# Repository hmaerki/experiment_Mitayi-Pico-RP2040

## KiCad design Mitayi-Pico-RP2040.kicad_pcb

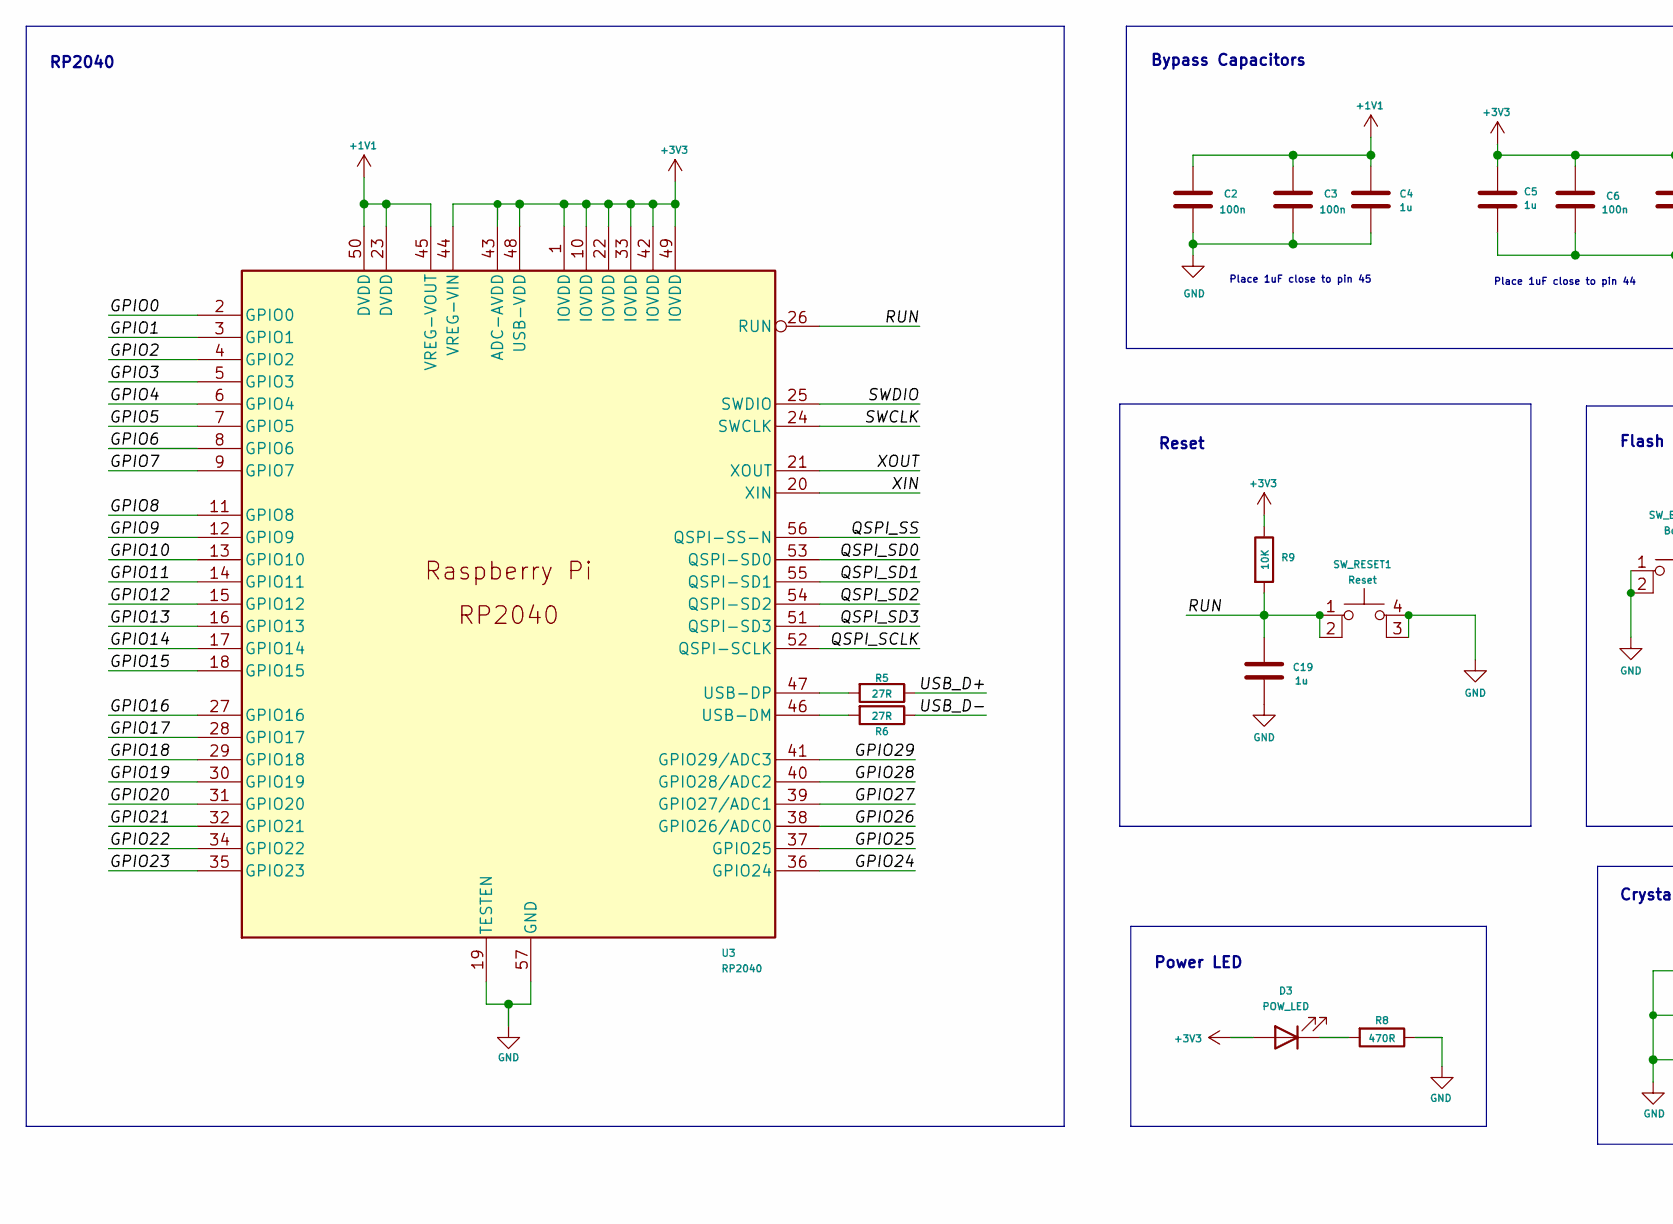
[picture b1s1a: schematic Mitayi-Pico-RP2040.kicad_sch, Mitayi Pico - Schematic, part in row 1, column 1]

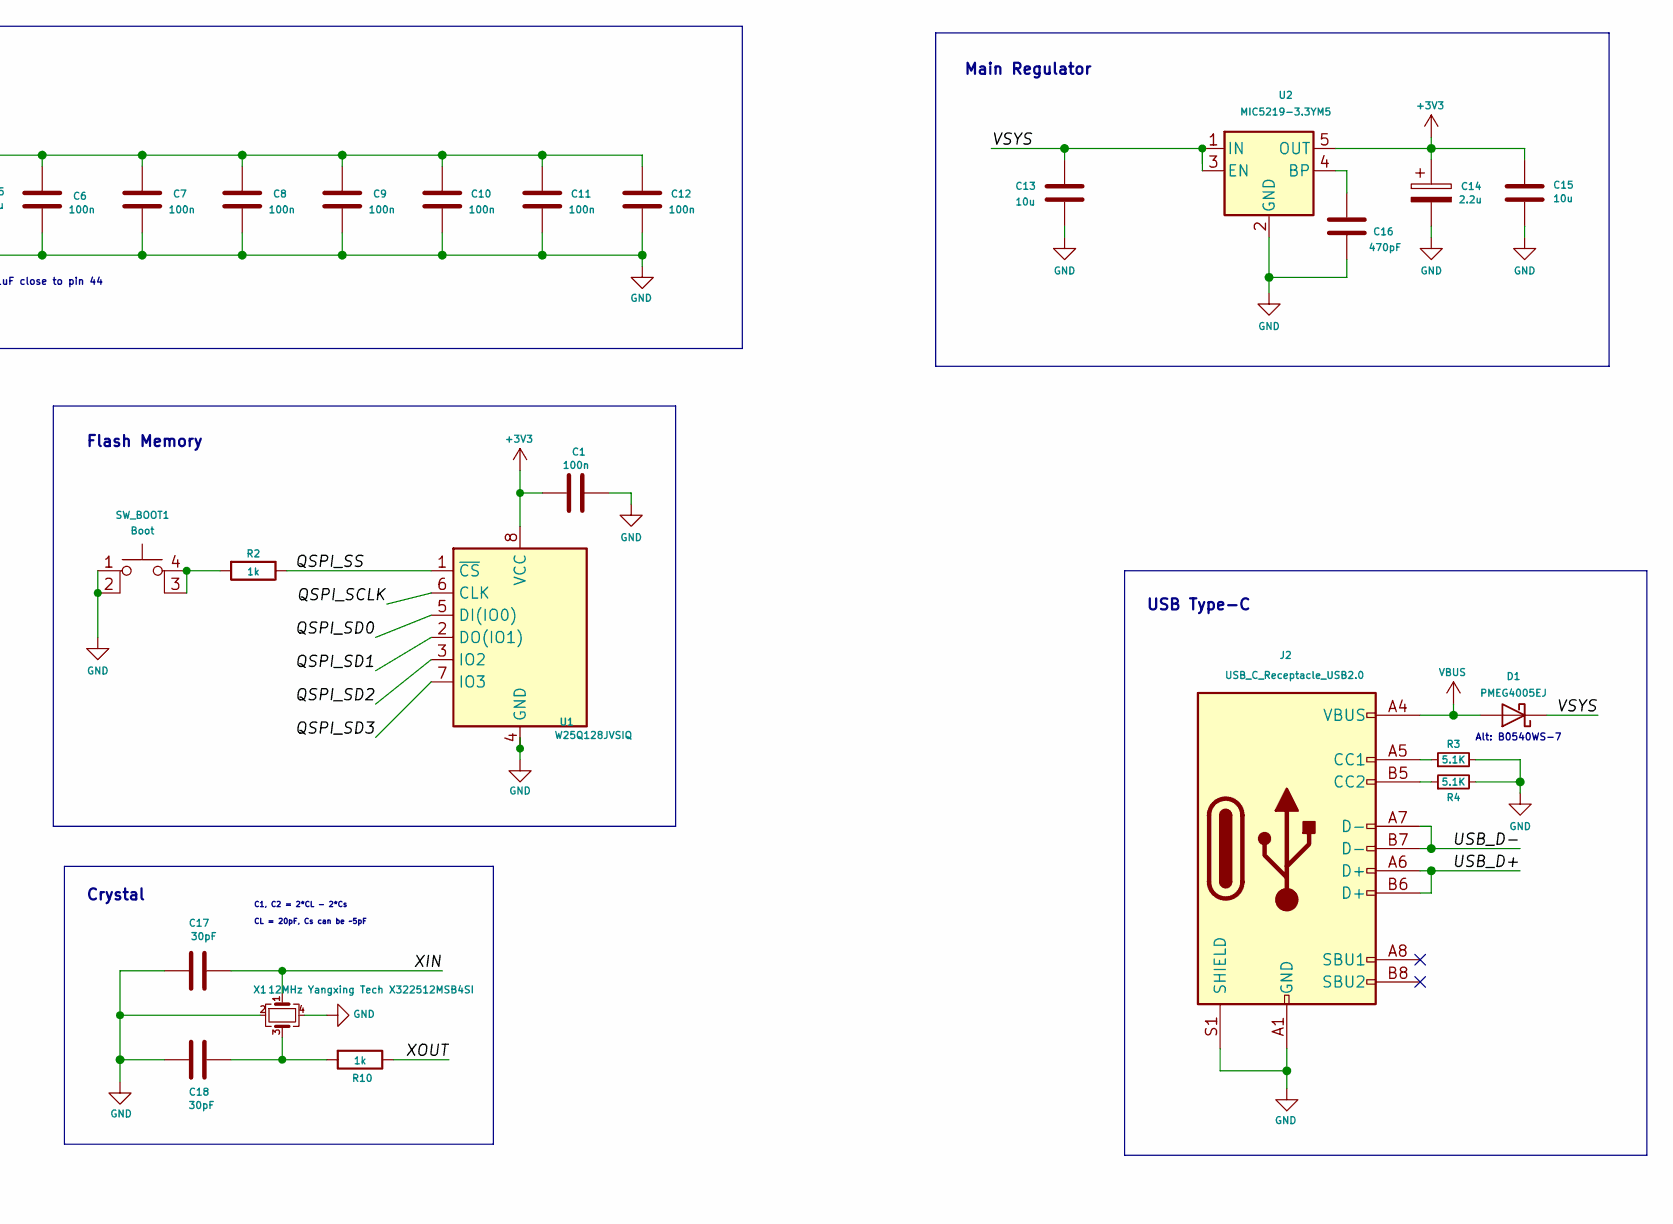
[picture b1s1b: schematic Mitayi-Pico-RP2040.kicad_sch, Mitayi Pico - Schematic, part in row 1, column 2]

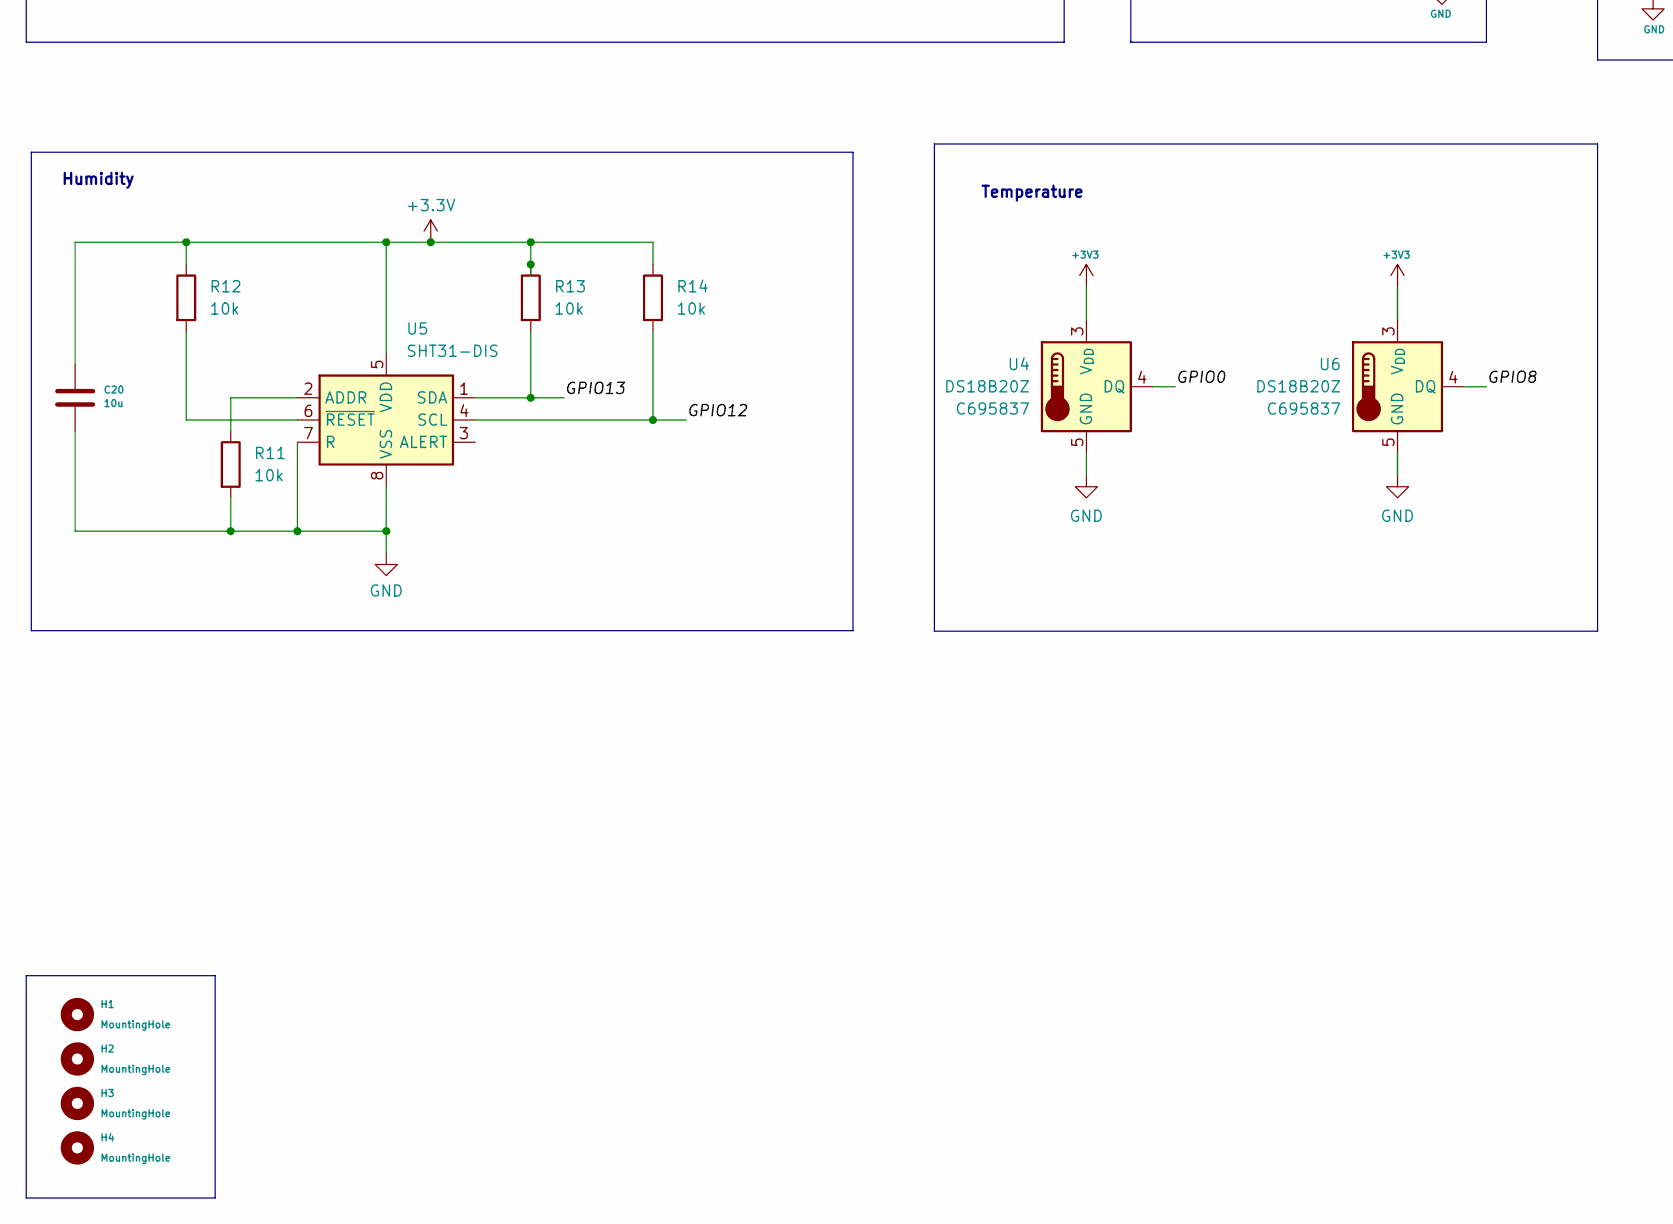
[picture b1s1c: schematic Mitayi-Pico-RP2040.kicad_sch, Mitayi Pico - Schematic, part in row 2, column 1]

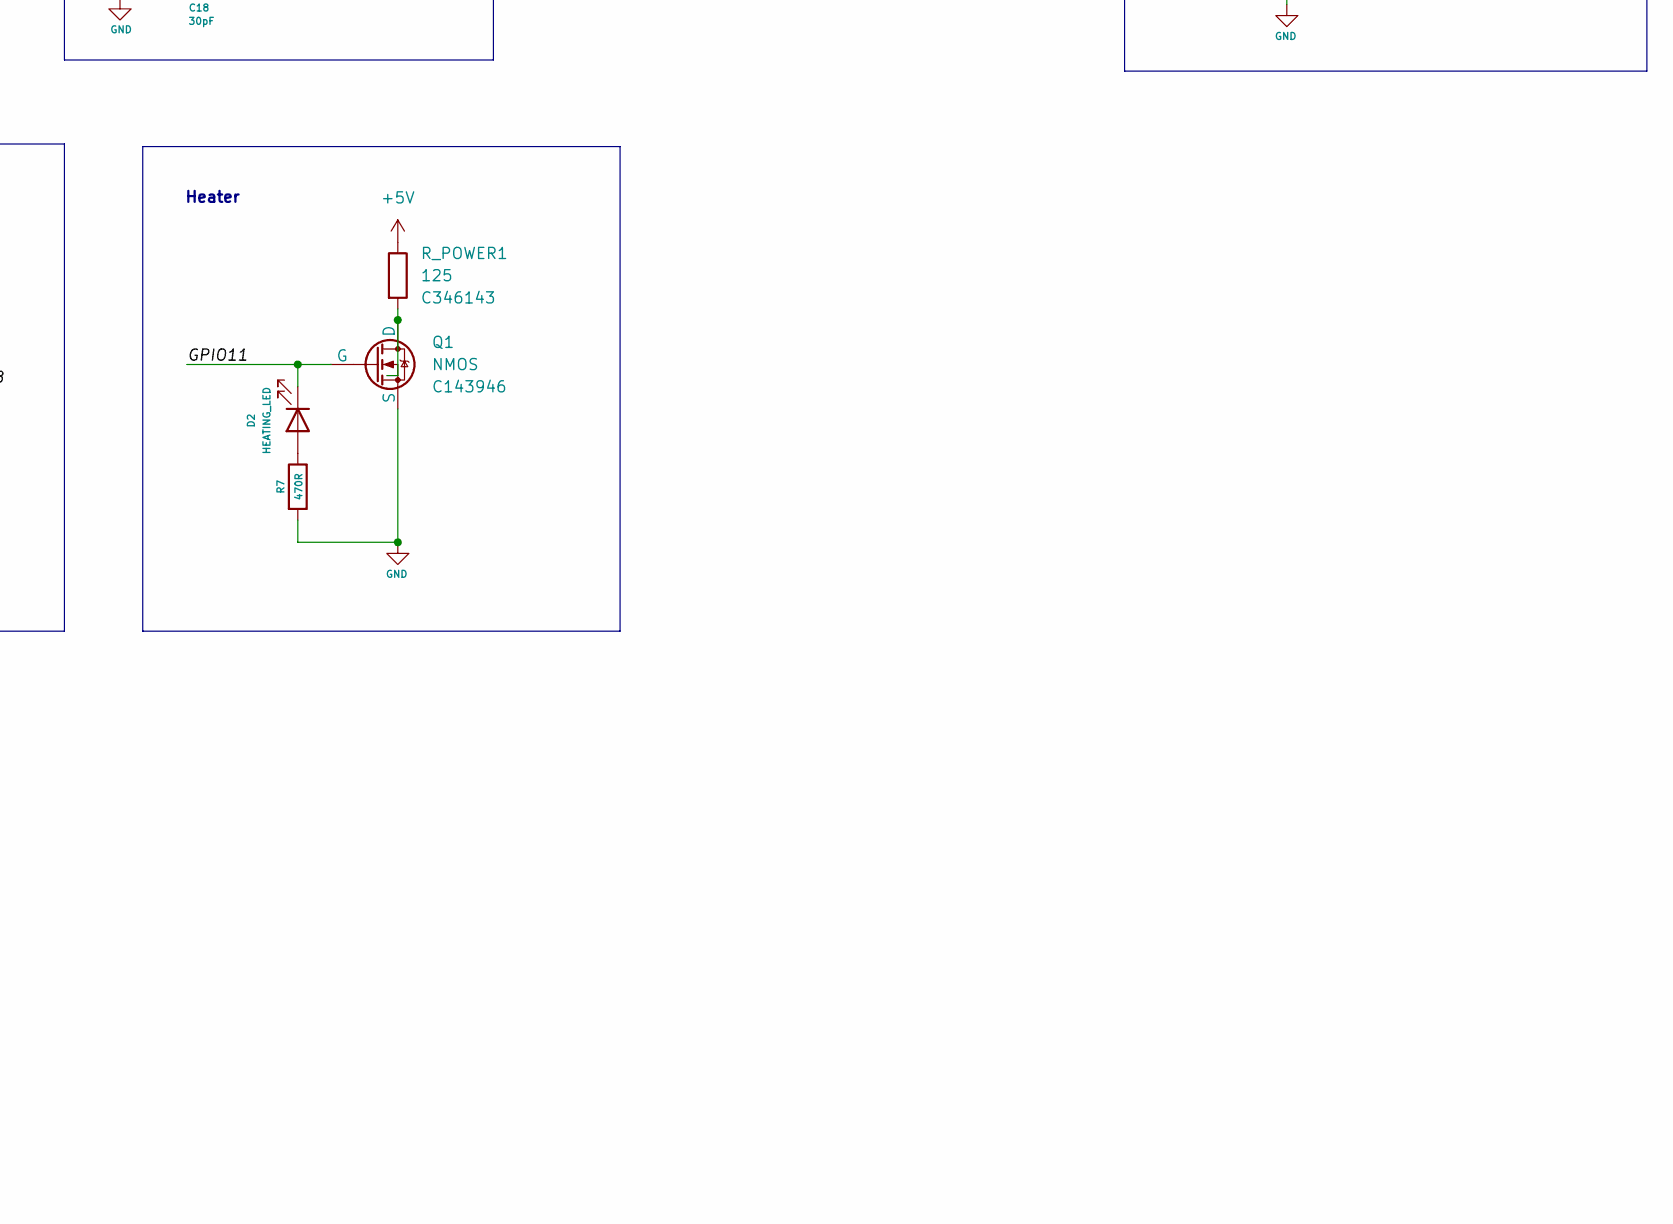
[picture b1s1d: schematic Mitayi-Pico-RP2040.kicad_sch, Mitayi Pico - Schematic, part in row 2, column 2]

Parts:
C1, C2, C3, C6, C7, C8, C9, C10, C11, C12: 100n; C_0402_1005Metric_Pad0.74x0.62mm_HandSolder
C4, C5, C19: 1u; C_0402_1005Metric_Pad0.74x0.62mm_HandSolder
C13, C15, C20: 10u; C_0603_1608Metric
C14: 2.2u; C_0402_1005Metric; JLC C12530
C16: 470pF; C_0402_1005Metric_Pad0.74x0.62mm_HandSolder
C17, C18: 30pF; C_0402_1005Metric_Pad0.74x0.62mm_HandSolder
D1: PMEG4005EJ; D_SOD-123F
D2: HEATING_LED; LED_0603_1608Metric
D3: POW_LED; LED_0603_1608Metric
H1, H2, H3, H4: MountingHole; MountingHole_2.2mm_M2
J2: USB_C_Receptacle_USB2.0; Korean-Hroparts-Elec_TYPE-C-31-M-12; JLC C5337088
Q1: NMOS; SOT-23; JLC Part C143946
R2, R10: 1k; R_0402_1005Metric_Pad0.72x0.64mm_HandSolder
R3, R4: 5.1K; R_0402_1005Metric_Pad0.72x0.64mm_HandSolder
R5, R6: 27R; R_0402_1005Metric_Pad0.72x0.64mm_HandSolder
R7, R8: 470R; R_0402_1005Metric_Pad0.72x0.64mm_HandSolder
R9: 10K; R_0402_1005Metric_Pad0.72x0.64mm_HandSolder
R11, R12, R13, R14: 10k; R_0402_1005Metric_Pad0.72x0.64mm_HandSolder
R_POWER1: 125; R_1210_3225Metric; JLC Part C346143
SW_BOOT1: Boot; SW_TS-1187A-B-A-B; JLC C318884
SW_RESET1: Reset; SW_TS-1187A-B-A-B; JLC C318884
U1: W25Q128JVSIQ; SOIC-8_5.23x5.23mm_P1.27mm
U2: MIC5219-3.3YM5; SOT-23-5
U3: RP2040; RP2040-QFN-56
U4, U6: DS18B20Z; SOIC-8_3.9x4.9mm_P1.27mm; JLC Part C695837
U5: SHT31-DIS; SON50P250X250X90-9T110X180N; JLC C80862
X1: 12MHz Yangxing Tech X322512MSB4SI; Crystal_SMD_3225-4Pin_3.2x2.5mm; JLC C9002

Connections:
+1V1: C2.1, C3.1, C4.1, U3.23 (DVDD), U3.45 (VREG-VOUT), U3.50 (DVDD)
+3.3V: C20.1, R12.1, R13.1, R14.1, U5.5 (VDD)
+3V3: C1.1, C5.1, C6.1, C7.1, C8.1, C9.1, C10.1, C11.1, C12.1, C14.1, C15.1, D3.2 (A), R9.1, U1.8 (VCC), U2.5 (OUT), U3.1 (IOVDD), U3.10 (IOVDD), U3.22 (IOVDD), U3.33 (IOVDD), U3.42 (IOVDD), U3.43 (ADC-AVDD), U3.44 (VREG-VIN), U3.48 (USB-VDD), U3.49 (IOVDD), U4.3 (V_{DD}), U6.3 (V_{DD})
+5V: R_POWER1.1
/GPIO0: U3.2 (GPIO0), U4.4 (DQ)
/GPIO1: U3.3 (GPIO1)
/GPIO2: U3.4 (GPIO2)
/GPIO3: U3.5 (GPIO3)
/GPIO4: U3.6 (GPIO4)
/GPIO5: U3.7 (GPIO5)
/GPIO6: U3.8 (GPIO6)
/GPIO7: U3.9 (GPIO7)
/GPIO8: U3.11 (GPIO8), U6.4 (DQ)
/GPIO9: U3.12 (GPIO9)
/GPIO10: U3.13 (GPIO10)
/GPIO11: D2.1 (K), Q1.2 (G), U3.14 (GPIO11)
/GPIO12: R14.2, U3.15 (GPIO12), U5.4 (SCL)
/GPIO13: R13.2, U3.16 (GPIO13), U5.1 (SDA)
/GPIO14: U3.17 (GPIO14)
/GPIO15: U3.18 (GPIO15)
/GPIO16: U3.27 (GPIO16)
/GPIO17: U3.28 (GPIO17)
/GPIO18: U3.29 (GPIO18)
/GPIO19: U3.30 (GPIO19)
/GPIO20: U3.31 (GPIO20)
/GPIO21: U3.32 (GPIO21)
/GPIO22: U3.34 (GPIO22)
/GPIO23: U3.35 (GPIO23)
/GPIO24: U3.36 (GPIO24)
/GPIO25: U3.37 (GPIO25)
/GPIO26: U3.38 (GPIO26/ADC0)
/GPIO27: U3.39 (GPIO27/ADC1)
/GPIO28: U3.40 (GPIO28/ADC2)
/GPIO29: U3.41 (GPIO29/ADC3)
/QSPI_SCLK: U1.6 (CLK), U3.52 (QSPI-SCLK)
/QSPI_SD0: U1.5 (DI(IO0)), U3.53 (QSPI-SD0)
/QSPI_SD1: U1.2 (DO(IO1)), U3.55 (QSPI-SD1)
/QSPI_SD2: U1.3 (IO2), U3.54 (QSPI-SD2)
/QSPI_SD3: U1.7 (IO3), U3.51 (QSPI-SD3)
/QSPI_SS: R2.1, U1.1 (~CS), U3.56 (QSPI-SS-N)
/RUN: C19.1, R9.2, SW_RESET1.1, SW_RESET1.2, U3.26 (RUN)
/SWCLK: U3.24 (SWCLK)
/SWDIO: U3.25 (SWDIO)
/USB_D+: J2.A6 (D+), J2.B6 (D+), R5.1
/USB_D-: J2.A7 (D-), J2.B7 (D-), R6.1
/VSYS: C13.1, D1.1 (K), U2.1 (IN), U2.3 (EN)
/XIN: C17.1, U3.20 (XIN), X1.1
/XOUT: R10.1, U3.21 (XOUT)
GND: C1.2, C2.2, C4.2, C5.2, C6.2, C7.2, C8.2, C9.2, C10.2, C11.2, C12.2, C13.2, C14.2, C15.2, C16.2, C17.2, C18.2, C19.2, C20.2, J2.A1 (GND), J2.A12 (GND), J2.B1 (GND), J2.B12 (GND), J2.S1 (SHIELD), Q1.3 (S), R3.2, R4.2, R7.2, R8.1, R11.2, SW_BOOT1.1, SW_BOOT1.2, SW_RESET1.3 (K), SW_RESET1.4 (A), U1.4 (GND), U2.2 (GND), U3.19 (TESTEN), U3.57 (GND), U4.5 (GND), U5.7 (R), U5.8 (VSS), U5.9 (VSS), U6.5 (GND), X1.2, X1.4
unnamed: C18.1, R10.2, X1.3
unnamed: D2.2 (A), R7.1
unnamed: D3.1 (K), R8.2
unnamed: J2.A5 (CC1), R3.1
unnamed: J2.B5 (CC2), R4.1
unnamed: Q1.1 (D), R_POWER1.2
unnamed: R2.2, SW_BOOT1.3 (K), SW_BOOT1.4 (A)
unnamed: C16.1, U2.4 (BP)
unnamed: R6.2, U3.46 (USB-DM)
unnamed: R5.2, U3.47 (USB-DP)
unnamed: R11.1, U5.2 (ADDR)
unnamed: R12.2, U5.6 (~RESET)
VBUS: D1.2 (A), J2.A4 (VBUS), J2.A9 (VBUS), J2.B4 (VBUS), J2.B9 (VBUS)

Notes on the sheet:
USB Type-C
Main Regulator
RP2040
Alt: B0540WS-7
Bypass Capacitors
Place 1uF close to pin 45
Heater
Crystal
Power LED
C1, C2 = 2*CL - 2*Cs CL = 20pF, Cs can be ~5pF
Reset
Place 1uF close to pin 44
Humidity
Flash Memory
Temperature

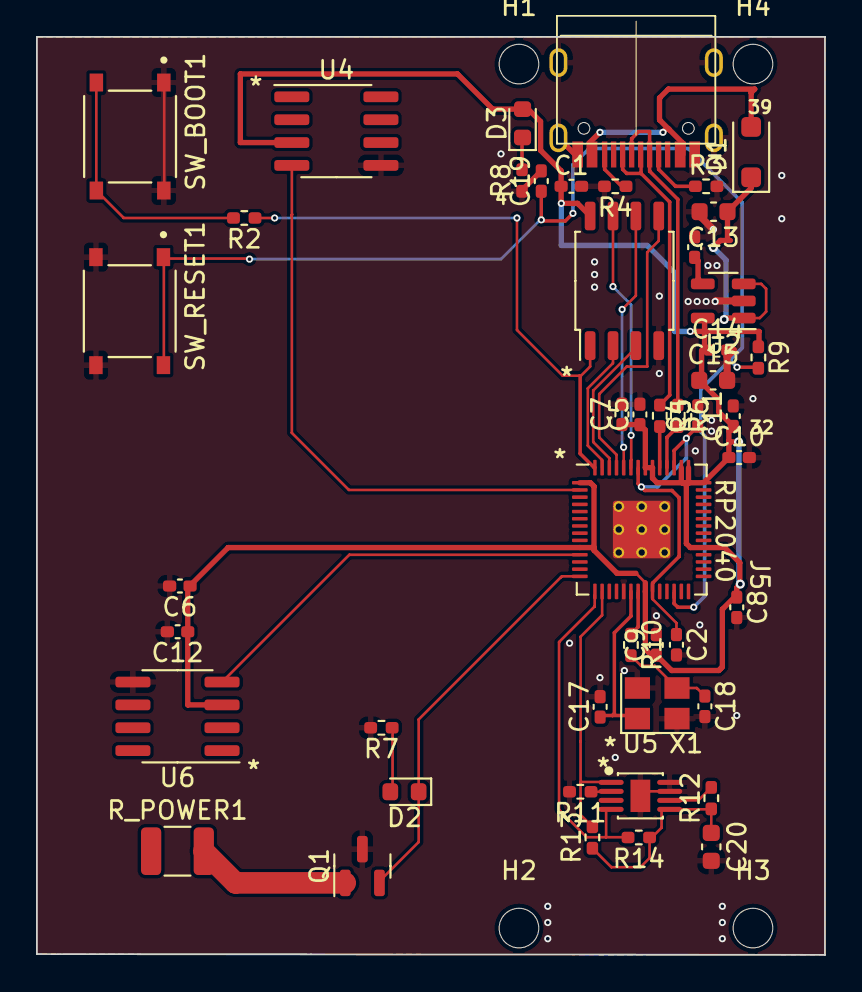
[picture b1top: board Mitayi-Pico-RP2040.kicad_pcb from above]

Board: 2 copper layers, 43.8 x 51.0 mm, 51 parts (0 on the bottom side), 34 nets.

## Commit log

2023-07-14 Remove headers and much more
2023-07-14 playing around with footprints
2023-07-14 Update footprints
2023-07-15 Simplyfix Boot Button
2023-07-15 Added more components
2023-07-15 Even more parts
2023-07-15 Cleanup

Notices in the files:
Mitayi-Pico-RP2040.kicad_pcb:
Copyright 2021-2023 CIRCUITSTATE Electronics LLP
Released under MIT Open-source License
parts and their libraries:
License: CC BY 4.0
